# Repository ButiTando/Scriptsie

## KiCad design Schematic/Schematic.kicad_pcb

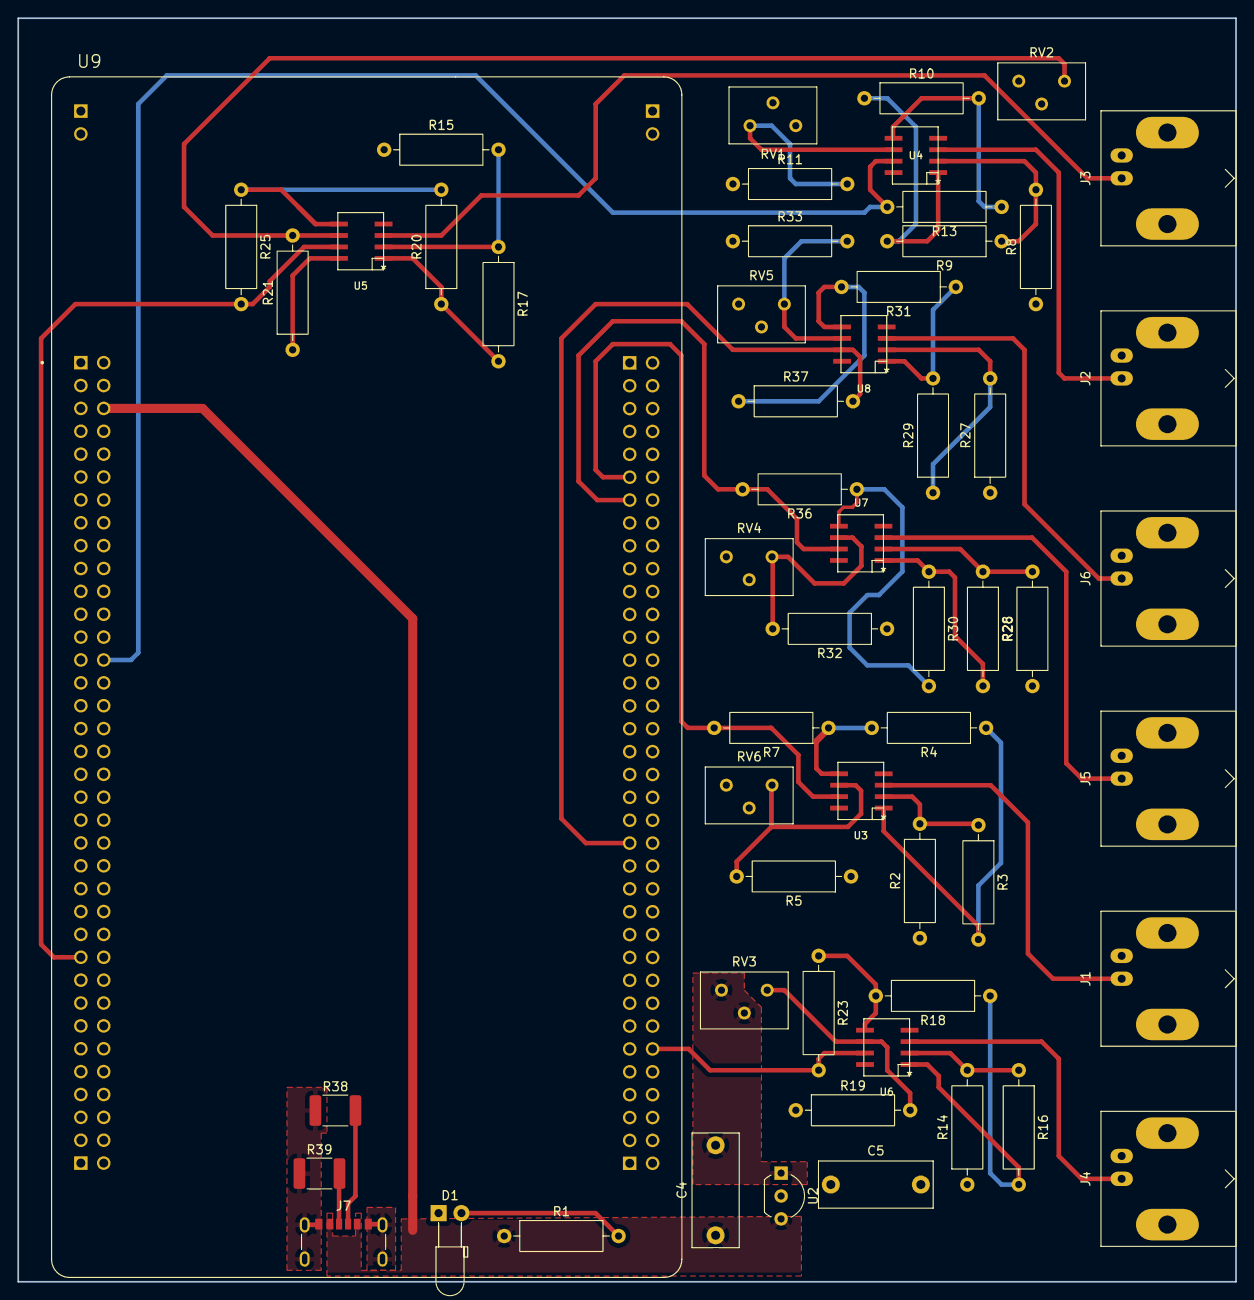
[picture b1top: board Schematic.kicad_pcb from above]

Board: 2 copper layers, 135.3 x 140.3 mm, 57 parts (0 on the bottom side), 42 nets.

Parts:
C4, C5: 1u; C_Disc_D12.5mm_W5.0mm_P10.00mm
D1: LED_RED; LED_D3.0mm_Horizontal_O3.81mm_Z2.0mm
J1, J2, J3, J4, J5, J6: Conn_Coaxial; BNC_Amphenol_B6252HB-NPP3G-50_Horizontal
J7: USB_C_Receptacle_PowerOnly_6P; USB_C_Receptacle_GCT_USB4125-xx-x_6P_TopMnt_Horizontal
R1: 660; R_Axial_DIN0309_L9.0mm_D3.2mm_P12.70mm_Horizontal
R2, R5, R8, R11, R14, R15, R19, R21, R26, R27, R32, R33: 10k; R_Axial_DIN0309_L9.0mm_D3.2mm_P12.70mm_Horizontal
R3, R9, R16, R17, R28, R29: 8.2k; R_Axial_DIN0309_L9.0mm_D3.2mm_P12.70mm_Horizontal
R4, R10, R18, R20, R30, R31: 15k; R_Axial_DIN0309_L9.0mm_D3.2mm_P12.70mm_Horizontal
R7, R13, R23, R25, R36, R37: 33k; R_Axial_DIN0309_L9.0mm_D3.2mm_P12.70mm_Horizontal
R38, R39: 5.1k; R_1812_4532Metric_Pad1.30x3.40mm_HandSolder
RV1, RV2, RV3, RV4, RV5, RV6: R_Potentiometer; Potentiometer_Bourns_3299Y_Vertical
U2: MCP1700x-330xxTO; TO-92_Inline_Wide
U3, U4, U5, U6, U7, U8: ADA4891-2ARZ-R7; SOIC8
U9: NUCLEOH723ZG; MODULE_NUCLEOH723ZG

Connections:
3V3: C5.1, R5.1, R11.1, R19.1, R21.1, R32.1, R33.1, U2.2 (VI), U3.P$8, U4.P$8, U5.P$8, U6.P$8, U7.P$8, U8.P$8
5V: C4.1, J7.A9 (VBUS), J7.B9 (VBUS), R1.1, U2.3 (VO), U9.CN11_6 (5V_EXT)
GND: C4.2, C5.2, D1.1 (K), J1.2 (Ext), J2.2 (Ext), J3.2 (Ext), J4.2 (Ext), J5.2 (Ext), J6.2 (Ext), J7.A12 (GND), J7.B12 (GND), J7.S1 (SHIELD), R2.1, R8.1, R14.1, R15.1, R26.1, R27.1, R38.1, R39.1, RV1.2, RV1.3, RV2.2, RV2.3, RV3.2, RV3.3, RV4.1, RV4.2, RV5.2, RV5.3, RV6.2, RV6.3, U2.1 (GND), U3.P$4, U4.P$4, U5.P$4, U6.P$4, U7.P$4, U8.P$4, U9.CN3_1 (GND_CN3), U9.CN3_2 (GND_CN3), U9.CN4_1 (GND_CN4), U9.CN4_2 (GND_CN4), U9.CN11_8 (GND_CN11), U9.CN11_19 (GND_CN11), U9.CN11_20 (GND_CN11), U9.CN11_22 (GND_CN11), U9.CN11_49 (GND_CN11), U9.CN11_60 (GND_CN11), U9.CN12_9 (GND_CN12), U9.CN12_20 (GND_CN12), U9.CN12_39 (GND_CN12), U9.CN12_54 (GND_CN12), U9.CN12_63 (GND_CN12), U9.CN15_1 (GND_CN15), U9.CN15_2 (GND_CN15), U9.CN16_1 (GND_CN16), U9.CN16_2 (GND_CN16)
unnamed: D1.2 (A), R1.2
unnamed: J1.1 (In), U3.P$3
unnamed: J2.1 (In), U4.P$3
unnamed: J3.1 (In), U5.P$3
unnamed: J4.1 (In), U6.P$3
unnamed: J5.1 (In), U7.P$3
unnamed: J6.1 (In), U8.P$3
unnamed: J7.A5 (CC1), R39.2
unnamed: J7.B5 (CC2), R38.2
unnamed: R2.2, R3.1, U3.P$2
unnamed: R3.2, R4.1, U3.P$1
unnamed: R4.2, R7.1, U3.P$5
unnamed: R5.2, RV6.1, U3.P$6
unnamed: R8.2, R9.1, U4.P$2
unnamed: R9.2, R10.1, U4.P$1
unnamed: R10.2, R13.1, U4.P$5
unnamed: R11.2, RV1.1, U4.P$6
unnamed: R14.2, R16.1, U6.P$2
unnamed: R15.2, R17.1, U5.P$2
unnamed: R16.2, R18.1, U6.P$1
unnamed: R17.2, R20.1, U5.P$1
unnamed: R18.2, R23.1, U6.P$5
unnamed: R19.2, RV3.1, U6.P$6
unnamed: R20.2, R25.1, U5.P$5
unnamed: R21.2, RV2.1, U5.P$6
unnamed: R26.2, R28.1, U7.P$2
unnamed: R27.2, R29.1, U8.P$2
unnamed: R28.2, R30.1, U7.P$1
unnamed: R29.2, R31.1, U8.P$1
unnamed: R30.2, R36.1, U7.P$5
unnamed: R31.2, R37.1, U8.P$5
unnamed: R32.2, RV4.3, U7.P$6
unnamed: R33.2, RV5.1, U8.P$6
pulse_out1: R7.2, U3.P$7, U9.CN12_11 (PA5)
pulse_out2: R13.2, U4.P$7, U9.CN11_28 (PA0)
pulse_out3: R25.2, U5.P$7, U9.CN11_53 (PF0)
pulse_out4: R23.2, U6.P$7, U9.CN12_62 (PF11)
pulse_out5: R36.2, U7.P$7, U9.CN12_13 (PA6)
pulse_out6: R37.2, U8.P$7, U9.CN12_43 (PD12)

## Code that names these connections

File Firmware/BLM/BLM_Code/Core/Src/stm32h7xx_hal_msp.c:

/* USER CODE BEGIN Header */
/**
  ******************************************************************************
  * @file         stm32h7xx_hal_msp.c
  * @brief        This file provides code for the MSP Initialization
  *               and de-Initialization codes.
  ******************************************************************************
  * @attention
  *
  * Copyright (c) 2025 STMicroelectronics.
  * All rights reserved.
  *
  * This software is licensed under terms that can be found in the LICENSE file
  * in the root directory of this software component.
  * If no LICENSE file comes with this software, it is provided AS-IS.
  *
  ******************************************************************************
  */
/* USER CODE END Header */

/* Includes ------------------------------------------------------------------*/
#include "main.h"
/* USER CODE BEGIN Includes */

/* USER CODE END Includes */

/* Private typedef -----------------------------------------------------------*/
/* USER CODE BEGIN TD */

/* USER CODE END TD */

/* Private define ------------------------------------------------------------*/
/* USER CODE BEGIN Define */

/* USER CODE END Define */

/* Private macro -------------------------------------------------------------*/
/* USER CODE BEGIN Macro */

/* USER CODE END Macro */

/* Private variables ---------------------------------------------------------*/
/* USER CODE BEGIN PV */

/* USER CODE END PV */

/* Private function prototypes -----------------------------------------------*/
/* USER CODE BEGIN PFP */

/* USER CODE END PFP */

/* External functions --------------------------------------------------------*/
/* USER CODE BEGIN ExternalFunctions */

/* USER CODE END ExternalFunctions */

/* USER CODE BEGIN 0 */

/* USER CODE END 0 */
/**
  * Initializes the Global MSP.
  */
void HAL_MspInit(void)
{

  /* USER CODE BEGIN MspInit 0 */

  /* USER CODE END MspInit 0 */

  __HAL_RCC_SYSCFG_CLK_ENABLE();

  /* System interrupt init*/

  /* USER CODE BEGIN MspInit 1 */

  /* USER CODE END MspInit 1 */
}

/**
  * @brief TIM_Base MSP Initialization
  * This function configures the hardware resources used in this example
  * @param htim_base: TIM_Base handle pointer
  * @retval None
  */
void HAL_TIM_Base_MspInit(TIM_HandleTypeDef* htim_base)
{
  GPIO_InitTypeDef GPIO_InitStruct = {0};
  if(htim_base->Instance==TIM2)
  {
    /* USER CODE BEGIN TIM2_MspInit 0 */

    /* USER CODE END TIM2_MspInit 0 */
    /* Peripheral clock enable */
    __HAL_RCC_TIM2_CLK_ENABLE();

    __HAL_RCC_GPIOA_CLK_ENABLE();
    /**TIM2 GPIO Configuration
    PA5     ------> TIM2_CH1
    */
    GPIO_InitStruct.Pin = GPIO_PIN_5;
    GPIO_InitStruct.Mode = GPIO_MODE_AF_PP;
    GPIO_InitStruct.Pull = GPIO_NOPULL;
    GPIO_InitStruct.Speed = GPIO_SPEED_FREQ_LOW;
    GPIO_InitStruct.Alternate = GPIO_AF1_TIM2;
    HAL_GPIO_Init(GPIOA, &GPIO_InitStruct);

    /* USER CODE BEGIN TIM2_MspInit 1 */

    /* USER CODE END TIM2_MspInit 1 */
  }
  else if(htim_base->Instance==TIM3)
  {
    /* USER CODE BEGIN TIM3_MspInit 0 */

    /* USER CODE END TIM3_MspInit 0 */
    /* Peripheral clock enable */
    __HAL_RCC_TIM3_CLK_ENABLE();

    __HAL_RCC_GPIOA_CLK_ENABLE();
    /**TIM3 GPIO Configuration
    PA6     ------> TIM3_CH1
    */
    GPIO_InitStruct.Pin = GPIO_PIN_6;
    GPIO_InitStruct.Mode = GPIO_MODE_AF_PP;
    GPIO_InitStruct.Pull = GPIO_NOPULL;
    GPIO_InitStruct.Speed = GPIO_SPEED_FREQ_LOW;
    GPIO_InitStruct.Alternate = GPIO_AF2_TIM3;
    HAL_GPIO_Init(GPIOA, &GPIO_InitStruct);

    /* USER CODE BEGIN TIM3_MspInit 1 */

    /* USER CODE END TIM3_MspInit 1 */
  }
  else if(htim_base->Instance==TIM4)
  {
    /* USER CODE BEGIN TIM4_MspInit 0 */

    /* USER CODE END TIM4_MspInit 0 */
    /* Peripheral clock enable */
    __HAL_RCC_TIM4_CLK_ENABLE();

    __HAL_RCC_GPIOD_CLK_ENABLE();
    /**TIM4 GPIO Configuration
    PD12     ------> TIM4_CH1
    */
    GPIO_InitStruct.Pin = GPIO_PIN_12;
    GPIO_InitStruct.Mode = GPIO_MODE_AF_PP;
    GPIO_InitStruct.Pull = GPIO_NOPULL;
    GPIO_InitStruct.Speed = GPIO_SPEED_FREQ_LOW;
    GPIO_InitStruct.Alternate = GPIO_AF2_TIM4;
    HAL_GPIO_Init(GPIOD, &GPIO_InitStruct);

    /* USER CODE BEGIN TIM4_MspInit 1 */

    /* USER CODE END TIM4_MspInit 1 */
  }
  else if(htim_base->Instance==TIM5)
  {
    /* USER CODE BEGIN TIM5_MspInit 0 */

    /* USER CODE END TIM5_MspInit 0 */
    /* Peripheral clock enable */
    __HAL_RCC_TIM5_CLK_ENABLE();

    __HAL_RCC_GPIOA_CLK_ENABLE();
    /**TIM5 GPIO Configuration
    PA0     ------> TIM5_CH1
    */
    GPIO_InitStruct.Pin = GPIO_PIN_0;
    GPIO_InitStruct.Mode = GPIO_MODE_AF_PP;
    GPIO_InitStruct.Pull = GPIO_NOPULL;
    GPIO_InitStruct.Speed = GPIO_SPEED_FREQ_LOW;
    GPIO_InitStruct.Alternate = GPIO_AF2_TIM5;
    HAL_GPIO_Init(GPIOA, &GPIO_InitStruct);

    /* USER CODE BEGIN TIM5_MspInit 1 */

    /* USER CODE END TIM5_MspInit 1 */
  }
  else if(htim_base->Instance==TIM23)
  {
    /* USER CODE BEGIN TIM23_MspInit 0 */

    /* USER CODE END TIM23_MspInit 0 */
    /* Peripheral clock enable */
    __HAL_RCC_TIM23_CLK_ENABLE();

    __HAL_RCC_GPIOF_CLK_ENABLE();
    /**TIM23 GPIO Configuration
    PF0     ------> TIM23_CH1
    */
    GPIO_InitStruct.Pin = GPIO_PIN_0;
    GPIO_InitStruct.Mode = GPIO_MODE_AF_PP;
    GPIO_InitStruct.Pull = GPIO_NOPULL;
    GPIO_InitStruct.Speed = GPIO_SPEED_FREQ_LOW;
    GPIO_InitStruct.Alternate = GPIO_AF13_TIM23;
    HAL_GPIO_Init(GPIOF, &GPIO_InitStruct);

    /* USER CODE BEGIN TIM23_MspInit 1 */

    /* USER CODE END TIM23_MspInit 1 */
  }
  else if(htim_base->Instance==TIM24)
  {
    /* USER CODE BEGIN TIM24_MspInit 0 */

    /* USER CODE END TIM24_MspInit 0 */
    /* Peripheral clock enable */
    __HAL_RCC_TIM24_CLK_ENABLE();

    __HAL_RCC_GPIOF_CLK_ENABLE();
    /**TIM24 GPIO Configuration
    PF11     ------> TIM24_CH1
    */
    GPIO_InitStruct.Pin = GPIO_PIN_11;
    GPIO_InitStruct.Mode = GPIO_MODE_AF_PP;
    GPIO_InitStruct.Pull = GPIO_NOPULL;
    GPIO_InitStruct.Speed = GPIO_SPEED_FREQ_LOW;
    GPIO_InitStruct.Alternate = GPIO_AF14_TIM24;
    HAL_GPIO_Init(GPIOF, &GPIO_InitStruct);

    /* USER CODE BEGIN TIM24_MspInit 1 */

    /* USER CODE END TIM24_MspInit 1 */
  }

}

/**
  * @brief TIM_Base MSP De-Initialization
  * This function freeze the hardware resources used in this example
  * @param htim_base: TIM_Base handle pointer
  * @retval None
  */
void HAL_TIM_Base_MspDeInit(TIM_HandleTypeDef* htim_base)
{
  if(htim_base->Instance==TIM2)
  {
    /* USER CODE BEGIN TIM2_MspDeInit 0 */

    /* USER CODE END TIM2_MspDeInit 0 */
    /* Peripheral clock disable */
    __HAL_RCC_TIM2_CLK_DISABLE();

    /**TIM2 GPIO Configuration
    PA5     ------> TIM2_CH1
    */
    HAL_GPIO_DeInit(GPIOA, GPIO_PIN_5);

    /* USER CODE BEGIN TIM2_MspDeInit 1 */

    /* USER CODE END TIM2_MspDeInit 1 */
  }
  else if(htim_base->Instance==TIM3)
  {
    /* USER CODE BEGIN TIM3_MspDeInit 0 */

    /* USER CODE END TIM3_MspDeInit 0 */
    /* Peripheral clock disable */
    __HAL_RCC_TIM3_CLK_DISABLE();

    /**TIM3 GPIO Configuration
    PA6     ------> TIM3_CH1
    */
    HAL_GPIO_DeInit(GPIOA, GPIO_PIN_6);

    /* USER CODE BEGIN TIM3_MspDeInit 1 */

    /* USER CODE END TIM3_MspDeInit 1 */
  }
  else if(htim_base->Instance==TIM4)
  {
    /* USER CODE BEGIN TIM4_MspDeInit 0 */

    /* USER CODE END TIM4_MspDeInit 0 */
    /* Peripheral clock disable */
    __HAL_RCC_TIM4_CLK_DISABLE();

    /**TIM4 GPIO Configuration
    PD12     ------> TIM4_CH1
    */
    HAL_GPIO_DeInit(GPIOD, GPIO_PIN_12);

    /* USER CODE BEGIN TIM4_MspDeInit 1 */

    /* USER CODE END TIM4_MspDeInit 1 */
  }
  else if(htim_base->Instance==TIM5)
  {
    /* USER CODE BEGIN TIM5_MspDeInit 0 */

    /* USER CODE END TIM5_MspDeInit 0 */
    /* Peripheral clock disable */
    __HAL_RCC_TIM5_CLK_DISABLE();

    /**TIM5 GPIO Configuration
    PA0     ------> TIM5_CH1
    */
    HAL_GPIO_DeInit(GPIOA, GPIO_PIN_0);

    /* USER CODE BEGIN TIM5_MspDeInit 1 */

    /* USER CODE END TIM5_MspDeInit 1 */
  }
  else if(htim_base->Instance==TIM23)
  {
    /* USER CODE BEGIN TIM23_MspDeInit 0 */

    /* USER CODE END TIM23_MspDeInit 0 */
    /* Peripheral clock disable */
    __HAL_RCC_TIM23_CLK_DISABLE();

    /**TIM23 GPIO Configuration
    PF0     ------> TIM23_CH1
    */
    HAL_GPIO_DeInit(GPIOF, GPIO_PIN_0);

    /* USER CODE BEGIN TIM23_MspDeInit 1 */

    /* USER CODE END TIM23_MspDeInit 1 */
  }
  else if(htim_base->Instance==TIM24)
  {
    /* USER CODE BEGIN TIM24_MspDeInit 0 */

    /* USER CODE END TIM24_MspDeInit 0 */
    /* Peripheral clock disable */
    __HAL_RCC_TIM24_CLK_DISABLE();

    /**TIM24 GPIO Configuration
    PF11     ------> TIM24_CH1
    */
    HAL_GPIO_DeInit(GPIOF, GPIO_PIN_11);

    /* USER CODE BEGIN TIM24_MspDeInit 1 */

    /* USER CODE END TIM24_MspDeInit 1 */
  }

}

/* USER CODE BEGIN 1 */

/* USER CODE END 1 */

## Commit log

2025-09-03 fix kiCad
2025-09-03 add nucleo to schematic
    Just add the nucleo to the schematic
2025-09-04 Add
    Add
2025-09-04 Add footprint to components
    Added footprint and 3D models to most of the component.
2025-09-04 Fix USB sheild connection
2025-09-04 Add BLM project
2025-09-05 fix nucleo footprint
2025-09-05 Add docs
2025-09-05 fix conflicts
2025-09-05 fix schematic and pcb layout
    Fix Potentiometer errors, and updated schematic
2025-09-05 Add updarw
    taking a break
2025-09-05 Add correct BLM project
    Created a new BLM project with timers and Ethernet set up. Timers are not in a functional state they are just chosen.
2025-09-06 Update PCB
